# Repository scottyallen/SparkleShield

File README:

The Sparkle Shield is an add-on shield for Arduino that has 70 individually
programmable full color LEDs arranged in a 7x10 matrix. It comes as an
unassembled kit that you can solder yourself with a few basic tools.  The
Sparkle Shield comes with a bunch of cool animations, but it's also easy to
program your own using the free Arduino development kit (compatible with
PC/Mac/Linux) and the Sparkle Shield Arduino library.

For more information and assembly and programming instructions, go to
http://sparkleshield.com.

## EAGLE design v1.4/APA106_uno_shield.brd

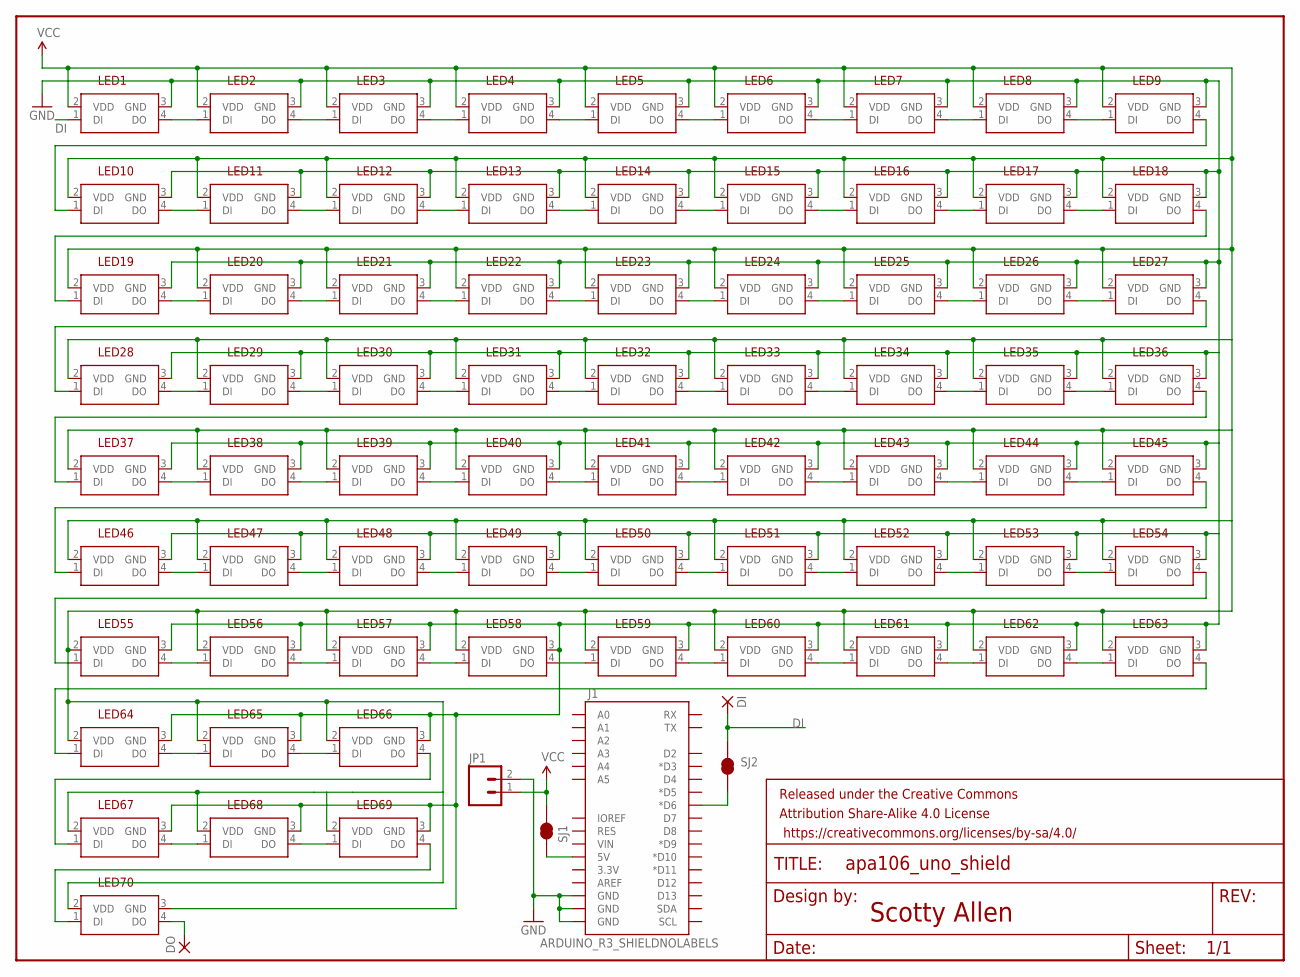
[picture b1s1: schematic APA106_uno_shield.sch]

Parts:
DI: 1,6/0,9
DO: 1,6/0,9
FRAME1: FRAME-LETTER; CREATIVE_COMMONS
J1: ARDUINO_R3_SHIELDNOLABELS; UNO_R3_SHIELD_NOLABELS
JP1: M02PTH; 1X02
LED1, LED2, LED3, LED4, LED5, LED6, LED7, LED8, LED9, LED10, LED11, LED12, LED13, LED14, LED15, LED16, LED17, LED18, LED19, LED20, LED21, LED22, LED23, LED24, LED25, LED26, LED27, LED28, LED29, LED30, LED31, LED32, LED33, LED34, LED35, LED36, LED37, LED38, LED39, LED40, LED41, LED42, LED43, LED44, LED45, LED46, LED47, LED48, LED49, LED50, LED51, LED52, LED53, LED54, LED55, LED56, LED57, LED58, LED59, LED60, LED61, LED62, LED63, LED64, LED65, LED66, LED67, LED68, LED69, LED70: LED-APA106HOLE-OFFSET-SPREAD; LED-5MM-4PIN-HOLE-OFFSET-SPREAD
SJ1, SJ2: JUMPER-PAD-2-NC_BY_TRACENO_SILK; PAD-JUMPER-2-NC_BY_TRACE_NO_SILK

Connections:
DI: DI.1, LED1.1 (DI), SJ2.2
GND: J1.GND@0 (GND), J1.GND@1 (GND), J1.GND@2 (GND), JP1.2, LED1.3 (GND), LED2.3 (GND), LED3.3 (GND), LED4.3 (GND), LED5.3 (GND), LED6.3 (GND), LED7.3 (GND), LED8.3 (GND), LED9.3 (GND), LED10.3 (GND), LED11.3 (GND), LED12.3 (GND), LED13.3 (GND), LED14.3 (GND), LED15.3 (GND), LED16.3 (GND), LED17.3 (GND), LED18.3 (GND), LED19.3 (GND), LED20.3 (GND), LED21.3 (GND), LED22.3 (GND), LED23.3 (GND), LED24.3 (GND), LED25.3 (GND), LED26.3 (GND), LED27.3 (GND), LED28.3 (GND), LED29.3 (GND), LED30.3 (GND), LED31.3 (GND), LED32.3 (GND), LED33.3 (GND), LED34.3 (GND), LED35.3 (GND), LED36.3 (GND), LED37.3 (GND), LED38.3 (GND), LED39.3 (GND), LED40.3 (GND), LED41.3 (GND), LED42.3 (GND), LED43.3 (GND), LED44.3 (GND), LED45.3 (GND), LED46.3 (GND), LED47.3 (GND), LED48.3 (GND), LED49.3 (GND), LED50.3 (GND), LED51.3 (GND), LED52.3 (GND), LED53.3 (GND), LED54.3 (GND), LED55.3 (GND), LED56.3 (GND), LED57.3 (GND), LED58.3 (GND), LED59.3 (GND), LED60.3 (GND), LED61.3 (GND), LED62.3 (GND), LED63.3 (GND), LED64.3 (GND), LED65.3 (GND), LED66.3 (GND), LED67.3 (GND), LED68.3 (GND), LED69.3 (GND), LED70.3 (GND)
unnamed: LED1.4 (DO), LED2.1 (DI)
unnamed: LED2.4 (DO), LED3.1 (DI)
unnamed: LED3.4 (DO), LED4.1 (DI)
unnamed: LED4.4 (DO), LED5.1 (DI)
unnamed: LED6.4 (DO), LED7.1 (DI)
unnamed: LED7.4 (DO), LED8.1 (DI)
unnamed: LED37.4 (DO), LED38.1 (DI)
unnamed: LED5.4 (DO), LED6.1 (DI)
unnamed: LED8.4 (DO), LED9.1 (DI)
unnamed: LED10.4 (DO), LED11.1 (DI)
unnamed: LED19.4 (DO), LED20.1 (DI)
unnamed: LED20.4 (DO), LED21.1 (DI)
unnamed: LED11.4 (DO), LED12.1 (DI)
unnamed: LED12.4 (DO), LED13.1 (DI)
unnamed: LED21.4 (DO), LED22.1 (DI)
unnamed: LED22.4 (DO), LED23.1 (DI)
unnamed: LED18.4 (DO), LED19.1 (DI)
unnamed: LED23.4 (DO), LED24.1 (DI)
unnamed: LED13.4 (DO), LED14.1 (DI)
unnamed: LED9.4 (DO), LED10.1 (DI)
unnamed: LED14.4 (DO), LED15.1 (DI)
unnamed: LED15.4 (DO), LED16.1 (DI)
unnamed: LED16.4 (DO), LED17.1 (DI)
unnamed: LED17.4 (DO), LED18.1 (DI)
unnamed: LED24.4 (DO), LED25.1 (DI)
unnamed: LED25.4 (DO), LED26.1 (DI)
unnamed: LED26.4 (DO), LED27.1 (DI)
unnamed: LED28.4 (DO), LED29.1 (DI)
unnamed: LED29.4 (DO), LED30.1 (DI)
unnamed: LED30.4 (DO), LED31.1 (DI)
unnamed: LED31.4 (DO), LED32.1 (DI)
unnamed: LED27.4 (DO), LED28.1 (DI)
unnamed: LED32.4 (DO), LED33.1 (DI)
unnamed: LED33.4 (DO), LED34.1 (DI)
unnamed: LED34.4 (DO), LED35.1 (DI)
unnamed: LED35.4 (DO), LED36.1 (DI)
unnamed: LED38.4 (DO), LED39.1 (DI)
unnamed: LED39.4 (DO), LED40.1 (DI)
unnamed: LED40.4 (DO), LED41.1 (DI)
unnamed: LED36.4 (DO), LED37.1 (DI)
unnamed: LED41.4 (DO), LED42.1 (DI)
unnamed: LED42.4 (DO), LED43.1 (DI)
unnamed: LED43.4 (DO), LED44.1 (DI)
unnamed: LED44.4 (DO), LED45.1 (DI)
unnamed: LED46.4 (DO), LED47.1 (DI)
unnamed: LED47.4 (DO), LED48.1 (DI)
unnamed: LED48.4 (DO), LED49.1 (DI)
unnamed: LED49.4 (DO), LED50.1 (DI)
unnamed: LED45.4 (DO), LED46.1 (DI)
unnamed: LED50.4 (DO), LED51.1 (DI)
unnamed: LED51.4 (DO), LED52.1 (DI)
unnamed: LED52.4 (DO), LED53.1 (DI)
unnamed: LED53.4 (DO), LED54.1 (DI)
unnamed: LED55.4 (DO), LED56.1 (DI)
unnamed: LED56.4 (DO), LED57.1 (DI)
unnamed: LED57.4 (DO), LED58.1 (DI)
unnamed: LED58.4 (DO), LED59.1 (DI)
unnamed: LED54.4 (DO), LED55.1 (DI)
unnamed: LED59.4 (DO), LED60.1 (DI)
unnamed: LED60.4 (DO), LED61.1 (DI)
unnamed: LED61.4 (DO), LED62.1 (DI)
unnamed: LED62.4 (DO), LED63.1 (DI)
unnamed: LED64.4 (DO), LED65.1 (DI)
unnamed: LED65.4 (DO), LED66.1 (DI)
unnamed: LED67.4 (DO), LED68.1 (DI)
unnamed: LED63.4 (DO), LED64.1 (DI)
unnamed: LED68.4 (DO), LED69.1 (DI)
unnamed: LED66.4 (DO), LED67.1 (DI)
unnamed: LED69.4 (DO), LED70.1 (DI)
unnamed: J1.5V, SJ1.1
unnamed: DO.1, LED70.4 (DO)
unnamed: J1.D6 (*D6), SJ2.1
VCC: JP1.1, LED1.2 (VDD), LED2.2 (VDD), LED3.2 (VDD), LED4.2 (VDD), LED5.2 (VDD), LED6.2 (VDD), LED7.2 (VDD), LED8.2 (VDD), LED9.2 (VDD), LED10.2 (VDD), LED11.2 (VDD), LED12.2 (VDD), LED13.2 (VDD), LED14.2 (VDD), LED15.2 (VDD), LED16.2 (VDD), LED17.2 (VDD), LED18.2 (VDD), LED19.2 (VDD), LED20.2 (VDD), LED21.2 (VDD), LED22.2 (VDD), LED23.2 (VDD), LED24.2 (VDD), LED25.2 (VDD), LED26.2 (VDD), LED27.2 (VDD), LED28.2 (VDD), LED29.2 (VDD), LED30.2 (VDD), LED31.2 (VDD), LED32.2 (VDD), LED33.2 (VDD), LED34.2 (VDD), LED35.2 (VDD), LED36.2 (VDD), LED37.2 (VDD), LED38.2 (VDD), LED39.2 (VDD), LED40.2 (VDD), LED41.2 (VDD), LED42.2 (VDD), LED43.2 (VDD), LED44.2 (VDD), LED45.2 (VDD), LED46.2 (VDD), LED47.2 (VDD), LED48.2 (VDD), LED49.2 (VDD), LED50.2 (VDD), LED51.2 (VDD), LED52.2 (VDD), LED53.2 (VDD), LED54.2 (VDD), LED55.2 (VDD), LED56.2 (VDD), LED57.2 (VDD), LED58.2 (VDD), LED59.2 (VDD), LED60.2 (VDD), LED61.2 (VDD), LED62.2 (VDD), LED63.2 (VDD), LED64.2 (VDD), LED65.2 (VDD), LED66.2 (VDD), LED67.2 (VDD), LED68.2 (VDD), LED69.2 (VDD), LED70.2 (VDD), SJ1.2

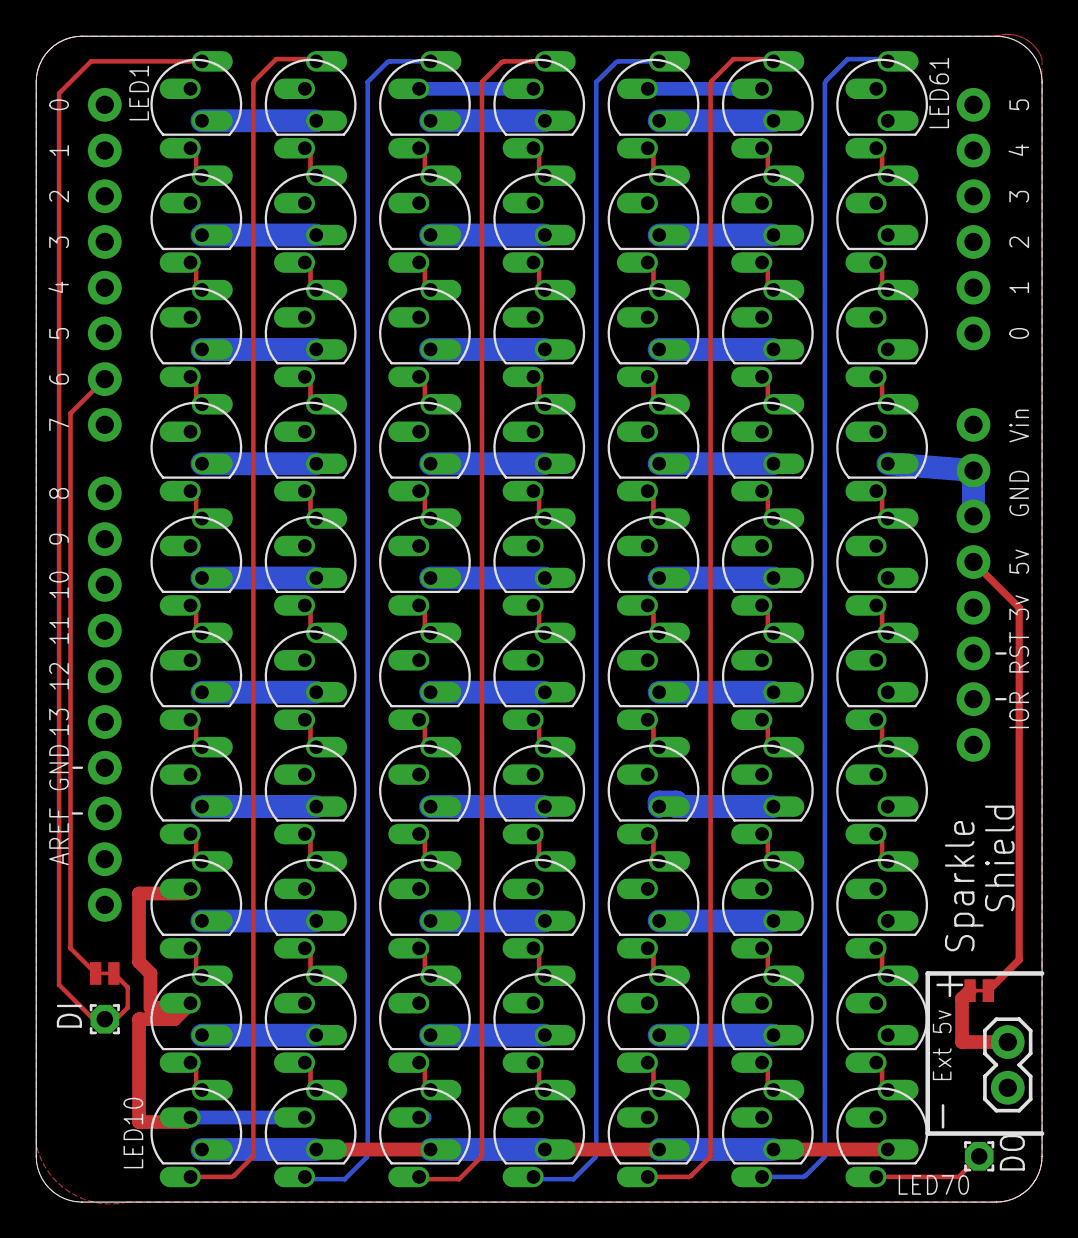
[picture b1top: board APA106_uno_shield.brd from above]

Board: 2 copper layers, 55.9 x 64.8 mm, 77 parts (0 on the bottom side), 75 nets.

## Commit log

2015-11-08 v2 of boards
2015-11-08 Add GPLv2 license
2015-11-16 Move v2 designs to v2 folder.
2015-11-16 final v3 board designs.
2015-12-24 A very simple animation to light each led in sequence.
2015-12-24 Clean up file comments and library keywords.
2015-12-24 Clean up pcb design files.
2015-12-24 Bundle arduino code as a zip file
2015-12-24 Add a README.
2015-12-24 v1.4 of board design
    - Changed name
    - Add url
    - make board narrower to allow better tiling of multiple boards.
2015-12-24 Setup an arduino library
2015-12-24 Working version of happy birthday scroller/rainbow
2015-12-24 Add library support for scrolling text.
2015-12-24 Extract scroll_text library call.
2015-12-24 Update to use library text scrolling support.
2015-12-24 Update to use scroll_text library method.
2015-12-24 Update library zip file.
2015-12-24 Matrix animation.
2015-12-28 Fix text scrolling example
2015-12-29 Update zip file
2016-01-03 Fixed typo that prevented compiling matrix example on Linux
2016-01-21 Add a plasma animation.
    Modified from the LoL Shield library, with tweaks for supporting the
    Sparkle Shield library, and for supporting multiple colors.
2016-01-21 Remove LaylaHappyBirthday.ino from master branch
2016-09-22 Fix problem compiling in Russian on Windows.
    For some reason, when the arduino IDE is set to Russian on Windows, it
    requires all functions to be declared before they are used.
    So this reorders functions in the examples to always define them before they are used.
2016-09-22 Demo animation that includes all the various examples.
    Restart the arduino (or hit the reset button) to go to the next animation.
2016-09-22 Double helix animation example.
2016-09-22 Fix zip file
2016-09-22 Fix Demo on Russian Windows.

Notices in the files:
v1.4/APA106_uno_shield.brd:
CC-BY-SA
parts and their libraries:
SparkFun-Aesthetics: Licensing: Creative Commons ShareAlike 4.0 International - https://creativecommons.org/licenses/by-sa/4.0
SparkFun-Aesthetics: Released under the Creative Commons Attribution Share-Alike 4.0 License
SparkFun-Aesthetics: https://creativecommons.org/licenses/by-sa/4.0
